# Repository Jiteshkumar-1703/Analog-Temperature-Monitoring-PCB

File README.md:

# Linearized Temperature Monitoring and Over-Temperature Alarm System (PCB)

## Overview
This project implements an analog temperature monitoring system using an NTC thermistor and op-amp based linearization. The circuit converts temperature variation into a near-linear voltage output and triggers an audible alarm when the temperature exceeds a preset threshold.

## Features
- NTC thermistor-based temperature sensing
- Op-amp based signal conditioning and linearization
- Comparator-based threshold detection
- Transistor-driven buzzer alarm
- 2-layer PCB designed using KiCad with ground copper pour

## Temperature Range
- 30 °C to 60 °C
- Alarm threshold set at 50 °C

## Tools Used
- KiCad (Schematic & PCB Design)
- Analog Circuit Design
- ERC & DRC verification

## Applications
- Over-temperature protection
- Industrial monitoring
- Embedded system front-end circuits

## Author
Jitesh Kumar

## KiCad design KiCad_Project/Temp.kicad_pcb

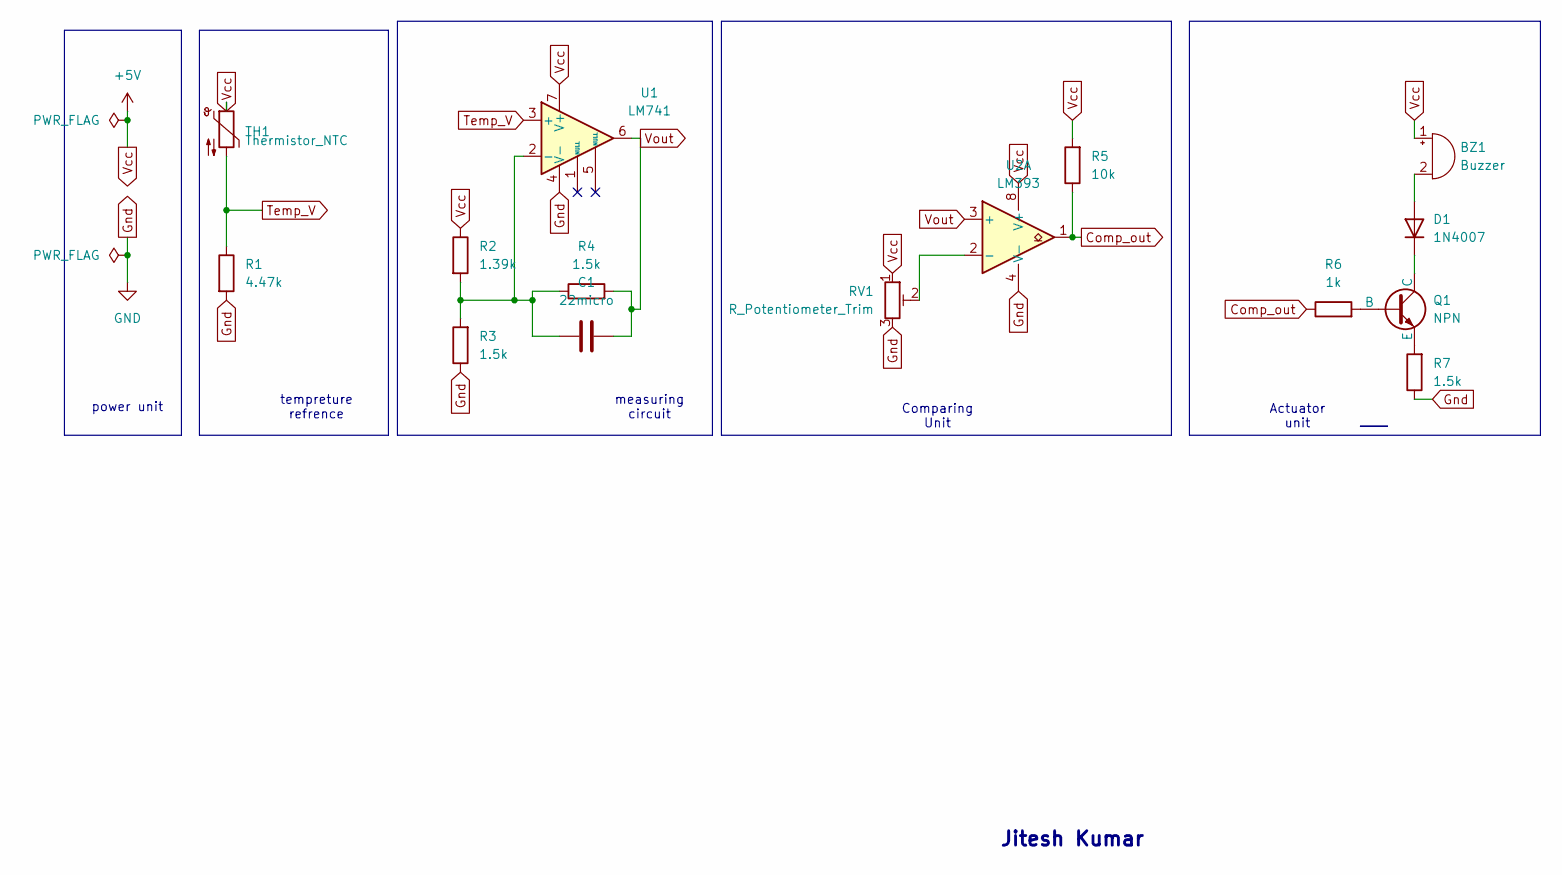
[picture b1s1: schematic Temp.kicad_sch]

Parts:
BZ1: Buzzer; Buzzer_TDK_PS1240P02BT_D12.2mm_H6.5mm
C1: 22micro; CP_Radial_D8.0mm_P3.50mm
D1: 1N4007; D_DO-41_SOD81_P10.16mm_Horizontal
Q1: NPN; TO-18-3
R1: 4.47k; R_0402_1005Metric_Pad0.72x0.64mm_HandSolder
R2: 1.39k; R_0402_1005Metric_Pad0.72x0.64mm_HandSolder
R3, R4, R7: 1.5k; C_1812_4532Metric_Pad1.57x3.40mm_HandSolder
R5: 10k; R_0402_1005Metric_Pad0.72x0.64mm_HandSolder
R6: 1k; R_0402_1005Metric_Pad0.72x0.64mm_HandSolder
RV1: R_Potentiometer_Trim; Potentiometer_Runtron_RM-065_Vertical
TH1: Thermistor_NTC; TestPoint_2Pads_Pitch5.08mm_Drill1.3mm
U1: LM741; DIP-8_W7.62mm
U2: LM393; DIP-8_W7.62mm

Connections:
Comp_out: R5.1, R6.1, U2.1
Gnd: R1.2, R3.1, R7.1, RV1.3, U1.4 (V-), U2.4 (V-)
unnamed: BZ1.2 (-), D1.2 (A)
unnamed: D1.1 (K), Q1.1 (C)
unnamed: Q1.2 (B), R6.2
unnamed: Q1.3 (E), R7.2
unnamed: C1.1, R2.2, R3.2, R4.1, U1.2 (-)
unnamed: RV1.2, U2.2 (-)
Temp_V: R1.1, TH1.2, U1.3 (+)
Vcc: BZ1.1 (+), R2.1, R5.2, RV1.1, TH1.1, U1.7 (V+), U2.8 (V+)
Vout: C1.2, R4.2, U1.6, U2.3 (+)

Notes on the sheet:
Actuator unit
Jitesh Kumar
tempreture refrence
measuring circuit
power unit
Comparing Unit

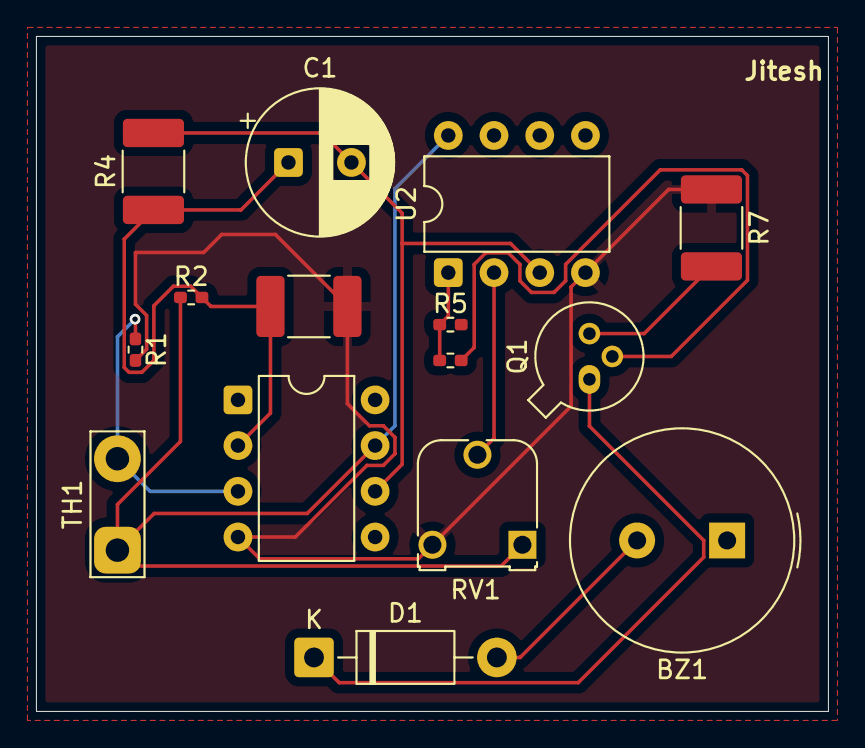
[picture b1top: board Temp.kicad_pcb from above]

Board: 2 copper layers, 44.0 x 37.5 mm, 15 parts (0 on the bottom side), 11 nets.

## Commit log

2025-12-28 README.md
